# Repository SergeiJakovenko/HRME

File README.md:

# HRME (Harness Resistor Matrix Encoder)

A multi-channel switching and encoding module based on MOSFET switches and VOM1271 optodrivers, designed in **KiCad**.

## 📌 Project Overview

The board features 9 independent load switching channels. Each channel utilizes a **VOM1271** photovoltaic optocoupler driver and an **IRLML6344** power MOSFET operating with precision resistor network/load circuits.

## 🛠 Specifications

* **Channels:** 9 independent channels[span_0](start_span)[span_0](end_span)

* **Power Supply:** +24V[span_1](start_span)[span_1](end_span)

* **Logic Control Voltage:** 5V[span_2](start_span)[span_2](end_span)

* **Key Components:**

&#x20; * Optodrivers: `VOM1271` (SOP-4)[span_3](start_span)[span_3](end_span)

&#x20; * Power MOSFETs: `IRLML6344` (SOT-23)[span_4](start_span)[span_4](end_span)

&#x20; * Resistors: Individual channel values ranging from 8.2 Ω to 2.2 kΩ[span_5](start_span)[span_5](end_span)

&#x20; * Connectors: Terminal blocks (`TZ0621038000G` \& `TZ0221018000G`)[span_6](start_span)[span_6](end_span)

## 📂 Repository Structure

* `HRME_V1.kicad_sch` - Schematic design file[span_7](start_span)[span_7](end_span)

* `HRME_V1.kicad_pcb` - PCB layout file[span_8](start_span)[span_8](end_span)[span_9](start_span)[span_9](end_span)

* `Libraries/` - Custom component symbols and footprint libraries

* `README.md` - Project documentation

## 🚀 How to Open

1. Install **KiCad** (v8.0 / v9.0+ recommended).

2. Clone or download this repository.

3. Open `HRME_V1.kicad_pro` using KiCad.

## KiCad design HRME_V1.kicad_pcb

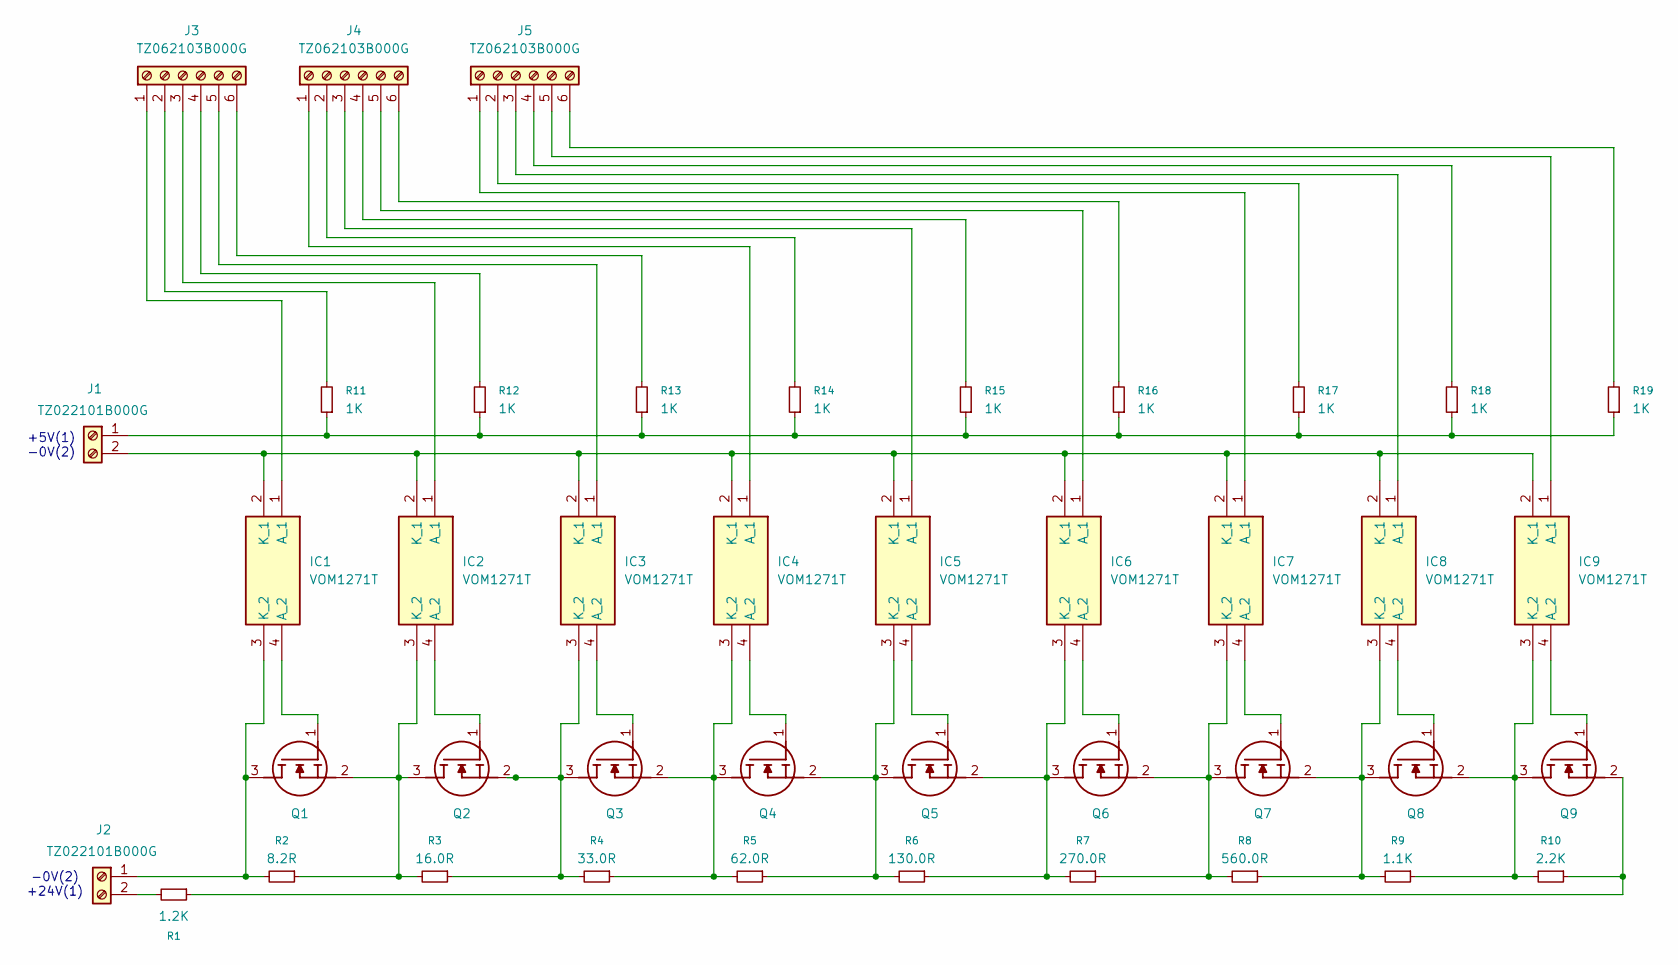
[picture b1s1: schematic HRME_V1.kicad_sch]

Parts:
IC1, IC2, IC3, IC4, IC5, IC6, IC7, IC8, IC9: VOM1271T; SOP254P675X240-4N; Manufacturer_Part_Number VOM1271T
J1, J2: TZ022101B000G
J3, J4, J5: TZ062103B000G
Q1, Q2, Q3, Q4, Q5, Q6, Q7, Q8, Q9: IRLML6344TRPBF; SOT95P237X112-3N; Manufacturer_Part_Number IRLML6344TRPBF
R1: 1.2K; R_1206_3216Metric
R2: 8.2R; R_1206_3216Metric
R3: 16.0R; R_1206_3216Metric
R4: 33.0R; R_1206_3216Metric
R5: 62.0R; R_1206_3216Metric
R6: 130.0R; R_1206_3216Metric
R7: 270.0R; R_1206_3216Metric
R8: 560.0R; R_1206_3216Metric
R9: 1.1K; R_1206_3216Metric
R10: 2.2K; R_1206_3216Metric
R11, R12, R13, R14, R15, R16, R17, R18, R19: 1K; R_1206_3216Metric

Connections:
unnamed: IC1.1 (A_1), J3.1
unnamed: IC1.4 (A_2), Q1.1 (G)
unnamed: IC1.2 (K_1), IC2.2 (K_1), IC3.2 (K_1), IC4.2 (K_1), IC5.2 (K_1), IC6.2 (K_1), IC7.2 (K_1), IC8.2 (K_1), IC9.2 (K_1), J1.2
unnamed: IC1.3 (K_2), J2.1, Q1.3 (D), R2.2
unnamed: IC2.1 (A_1), J3.3
unnamed: IC2.4 (A_2), Q2.1 (G)
unnamed: IC2.3 (K_2), Q1.2 (S), Q2.3 (D), R2.1, R3.2
unnamed: IC3.1 (A_1), J3.5
unnamed: IC3.4 (A_2), Q3.1 (G)
unnamed: IC3.3 (K_2), Q2.2 (S), Q3.3 (D), R3.1, R4.2
unnamed: IC4.1 (A_1), J4.1
unnamed: IC4.4 (A_2), Q4.1 (G)
unnamed: IC4.3 (K_2), Q3.2 (S), Q4.3 (D), R4.1, R5.2
unnamed: IC5.1 (A_1), J4.3
unnamed: IC5.4 (A_2), Q5.1 (G)
unnamed: IC5.3 (K_2), Q4.2 (S), Q5.3 (D), R5.1, R6.2
unnamed: IC6.1 (A_1), J4.5
unnamed: IC6.4 (A_2), Q6.1 (G)
unnamed: IC6.3 (K_2), Q5.2 (S), Q6.3 (D), R6.1, R7.2
unnamed: IC7.1 (A_1), J5.1
unnamed: IC7.4 (A_2), Q7.1 (G)
unnamed: IC7.3 (K_2), Q6.2 (S), Q7.3 (D), R7.1, R8.2
unnamed: IC8.1 (A_1), J5.3
unnamed: IC8.4 (A_2), Q8.1 (G)
unnamed: IC8.3 (K_2), Q7.2 (S), Q8.3 (D), R8.1, R9.2
unnamed: IC9.1 (A_1), J5.5
unnamed: IC9.4 (A_2), Q9.1 (G)
unnamed: IC9.3 (K_2), Q8.2 (S), Q9.3 (D), R9.1, R10.2
unnamed: J1.1, R11.1, R12.1, R13.1, R14.1, R15.1, R16.1, R17.1, R18.1, R19.1
unnamed: J2.2, R1.2
unnamed: J3.2, R11.2
unnamed: J3.4, R12.2
unnamed: J3.6, R13.2
unnamed: J4.2, R14.2
unnamed: J4.4, R15.2
unnamed: J4.6, R16.2
unnamed: J5.2, R17.2
unnamed: J5.4, R18.2
unnamed: J5.6, R19.2
unnamed: Q9.2 (S), R1.1, R10.1

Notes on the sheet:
-0V(2) +24V(1)
+5V(1) -0V(2)

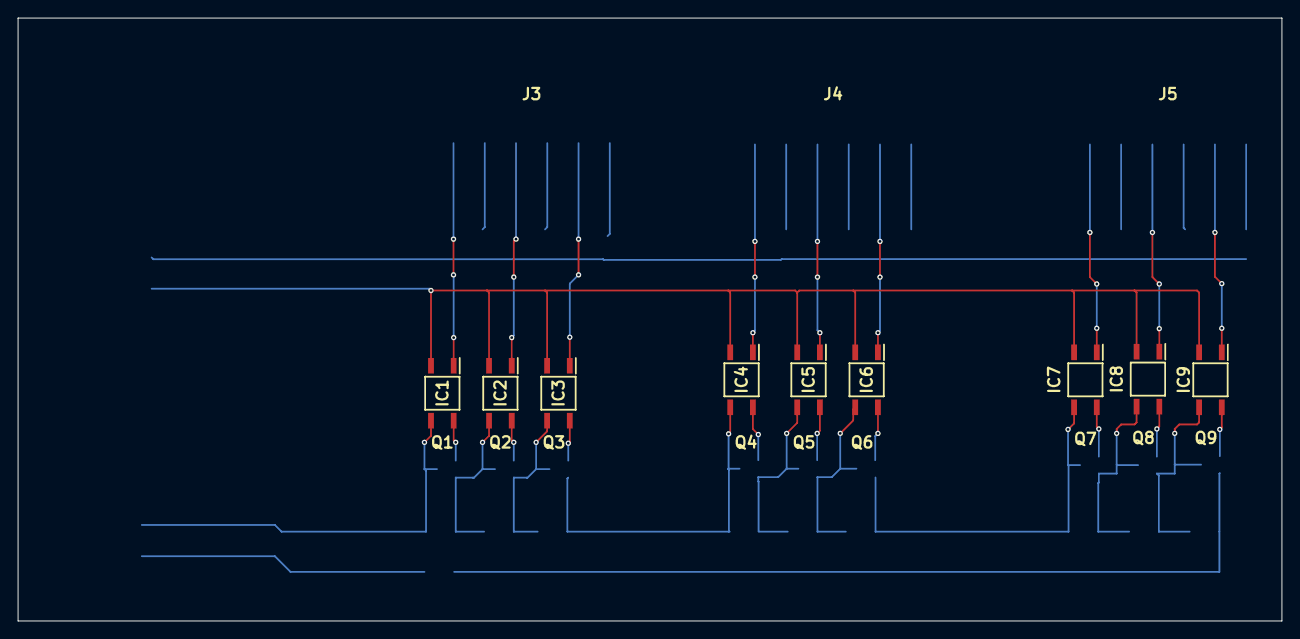
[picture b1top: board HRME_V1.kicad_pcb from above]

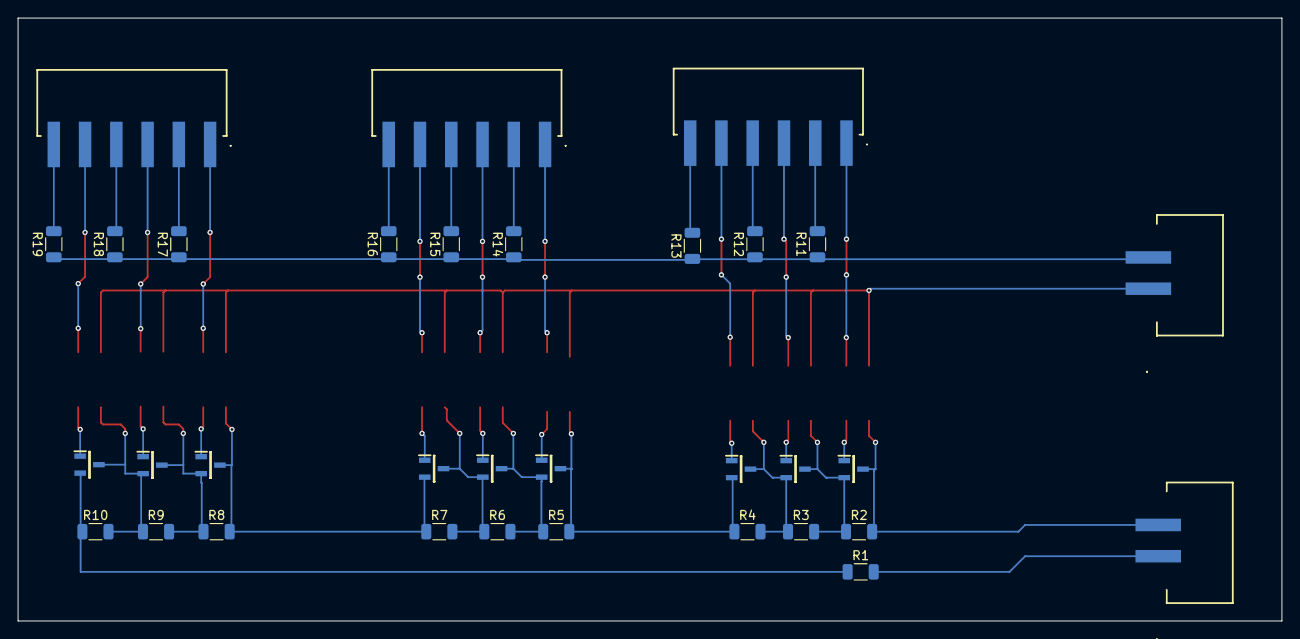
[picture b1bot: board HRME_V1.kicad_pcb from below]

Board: 2 copper layers, 141.5 x 67.5 mm, 42 parts (33 on the bottom side), 40 nets.
